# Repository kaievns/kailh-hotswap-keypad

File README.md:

# Kailh Choc Hot Swap v1/v2

This is a tiny PCB for individual Kailh Choc mechanical switches. It's meant for
hand wiring non-flat keyboards.

- Supports both v1 and v2 Chocs
- Has a hot-swap socket
- Has an LED socket for SK6812MINIs

**WANRNING** has 0602 size components and meant for PCB Assembly service

## Copyright & License

Everything is released under the terms of the CC BY-SA 4.0 license

© 2025 Kai Evans

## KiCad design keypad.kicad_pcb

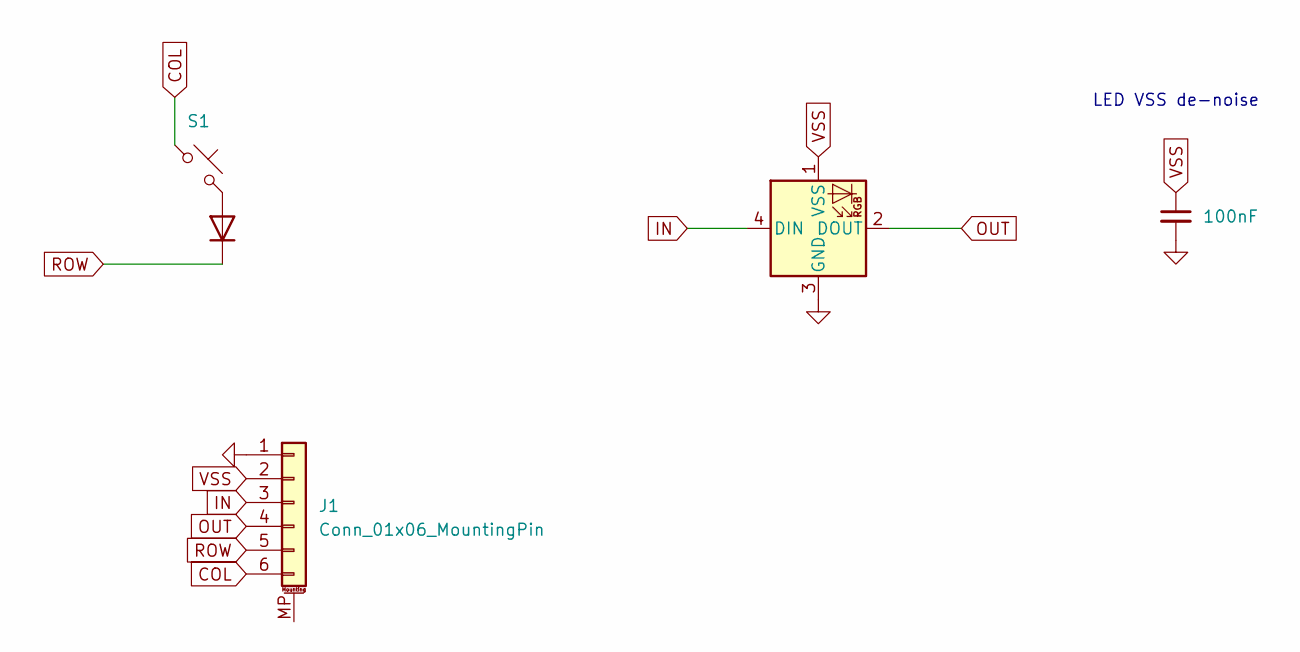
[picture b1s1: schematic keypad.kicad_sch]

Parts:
C1: 100nF; C_0603_1608Metric; LCSC C14663
D1: Diode; D_SOD-523; LCSC C83482
D2: LED_SK6812MINI; LCSC C5149201
J1: Conn_01x06_MountingPin; Hirose_FH19C-6S-0.5SH_1x06
S1: Keyswitch; Kailh_socket_PG1350

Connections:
COL: J1.6, S1.1
GND: C1.2, D2.3 (GND), J1.1
IN: D2.4 (DIN), J1.3
unnamed: D1.2 (A), S1.2
OUT: D2.2 (DOUT), J1.4
ROW: D1.1 (K), J1.5
VSS: C1.1, D2.1 (VSS), J1.2

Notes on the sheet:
LED VSS de-noise

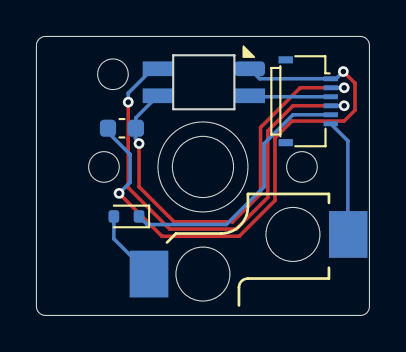
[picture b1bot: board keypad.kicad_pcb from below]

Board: 2 copper layers, 18.5 x 15.5 mm, 5 parts (4 on the bottom side), 7 nets.

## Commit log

2024-08-05 Initial setup
2024-08-07 Initial PCB layout
2024-08-07 Flipping the components in place
2024-08-09 Stashing the work before extending the cutouts
2024-08-20 Spit and polish
2024-08-25 Adding the left/right hand split
2024-08-26 Creating the reusable key pad
2024-08-29 Final touches for the mobos
2024-08-29 Rewiring the trackball sensor PCB
2024-09-17 Swapping out some components
2024-09-17 Reconnecting all the components on PCB again
2024-09-17 Rearranging things a bit
2024-10-05 Moving all the kicads into its own folder
2025-01-11 Throwing in the new PCB outline for the optical sensor
2025-01-18 Splitting the KiCAD project into thre independent PCBs
2025-03-29 Reworking the keypad PCB
2025-05-03 Stashing pcb changes
2025-09-24 Stashing the work
2025-12-13 Adding choc v2 support and VCC denoise cap
2025-12-13 BOM patches
2026-05-01 Swapping the socket model
